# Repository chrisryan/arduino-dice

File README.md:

#Arduino Dice LED Flasher

A simple project to randomly generate dice rolls with a arduino and show it as a 6 sided dice with LEDs.

Build the circuit and either update the code to your pin layout or attach pins according to the schematic.

Uses and arduino, 7 leds, 8 resistors, and a push button.

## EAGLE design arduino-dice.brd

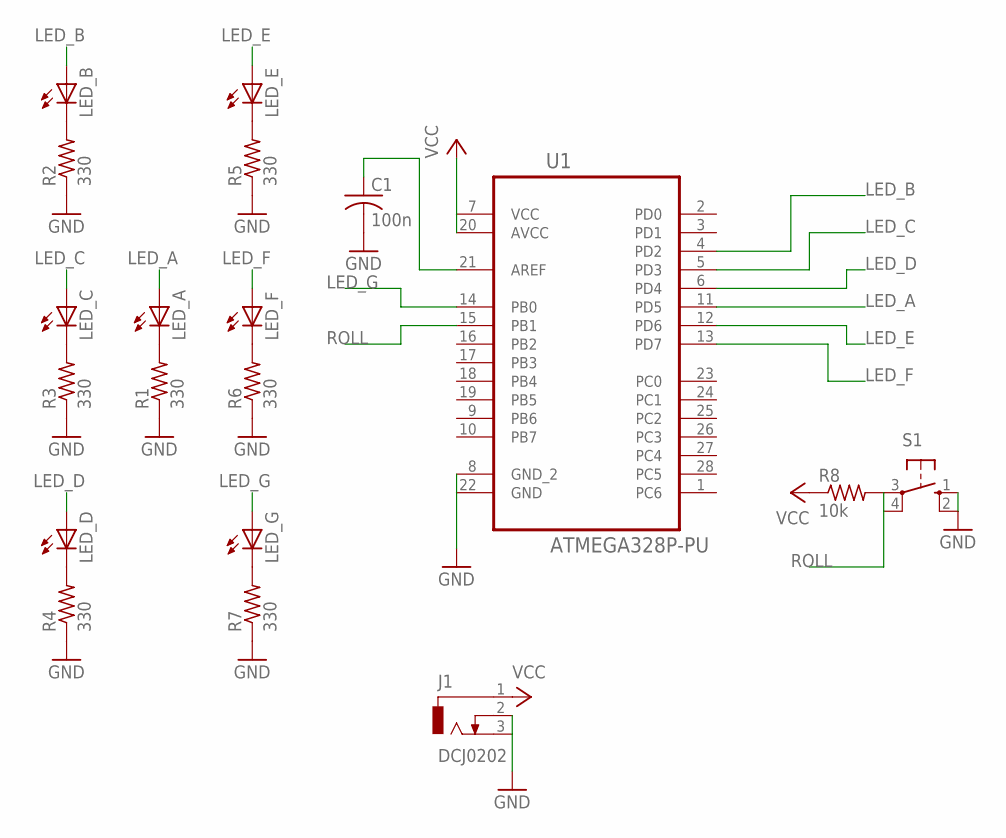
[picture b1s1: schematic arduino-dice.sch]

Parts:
C1: 100n; C050-024X044
J1: DCJ0202
LED_A: LED5MM
LED_B: LED5MM
LED_C: LED5MM
LED_D: LED5MM
LED_E: LED5MM
LED_F: LED5MM
LED_G: LED5MM
R1, R2, R3, R4, R5, R6, R7: 330; 0207/10
R8: 10k; 0207/10
S1: 10-XX; B3F-10XX
U1: ATMEGA328P-PU; DIP254P762X457-28

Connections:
GND: C1.2, J1.2, J1.3, R1.1, R2.1, R3.1, R4.1, R5.1, R6.1, R7.1, S1.1 (S), S1.2 (S1), U1.8 (GND_2), U1.22 (GND)
LED_A: LED_A.A, U1.11 (PD5)
LED_B: LED_B.A, U1.4 (PD2)
LED_C: LED_C.A, U1.5 (PD3)
LED_D: LED_D.A, U1.6 (PD4)
LED_E: LED_E.A, U1.12 (PD6)
LED_F: LED_F.A, U1.13 (PD7)
LED_G: LED_G.A, U1.14 (PB0)
unnamed: LED_A.K (C), R1.2
unnamed: LED_B.K (C), R2.2
unnamed: LED_C.K (C), R3.2
unnamed: LED_D.K (C), R4.2
unnamed: LED_E.K (C), R5.2
unnamed: LED_G.K (C), R7.2
unnamed: LED_F.K (C), R6.2
unnamed: C1.1, U1.21 (AREF)
ROLL: R8.2, S1.3, S1.4 (P1), U1.15 (PB1)
VCC: J1.1, R8.1, U1.7 (VCC), U1.20 (AVCC)

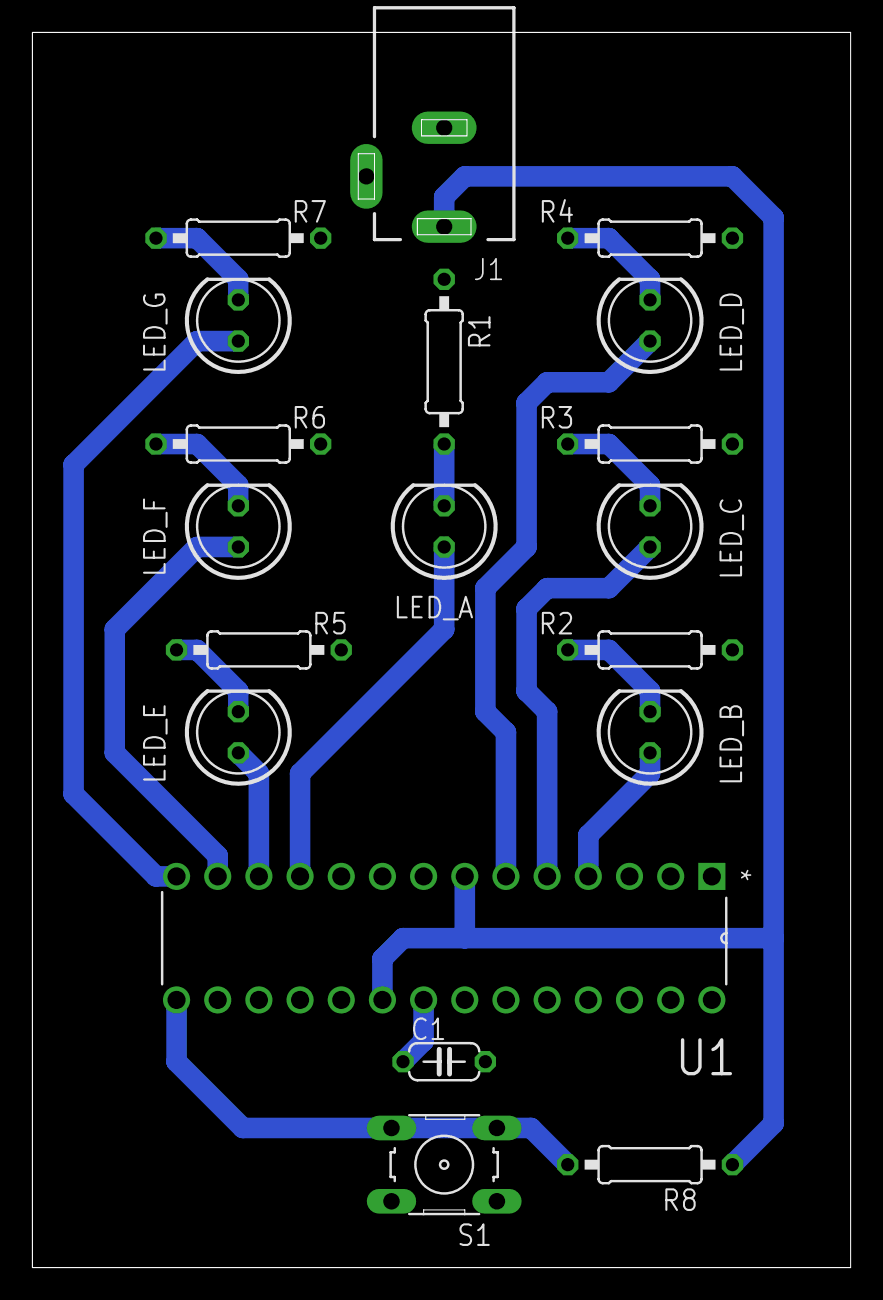
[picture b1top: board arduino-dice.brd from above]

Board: 2 copper layers, 50.5 x 76.2 mm, 19 parts (0 on the bottom side), 18 nets.

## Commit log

2015-05-10 REVISION 1
